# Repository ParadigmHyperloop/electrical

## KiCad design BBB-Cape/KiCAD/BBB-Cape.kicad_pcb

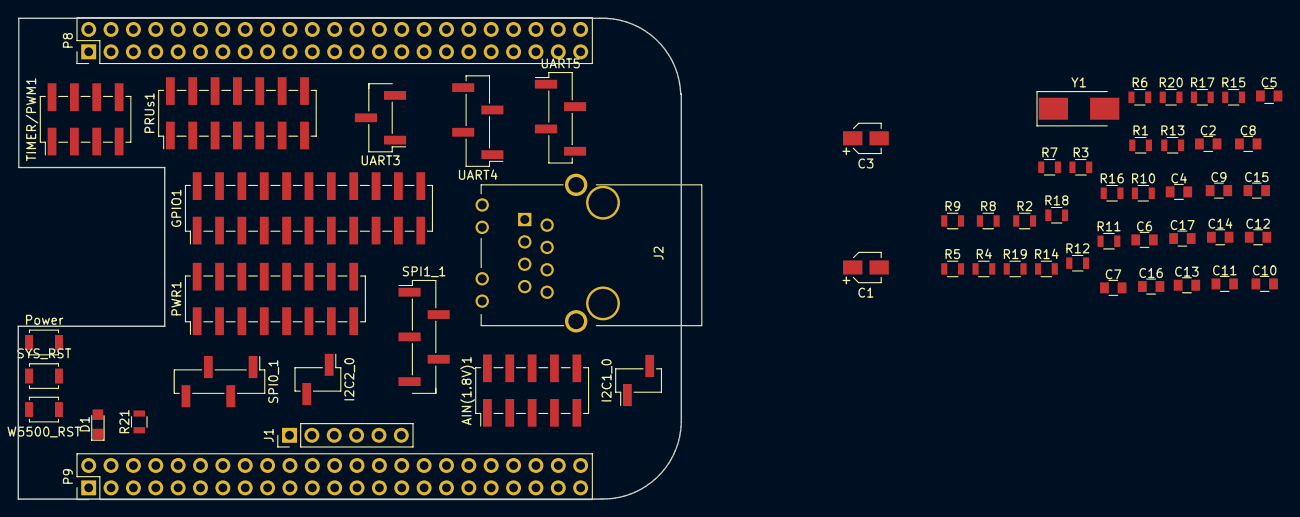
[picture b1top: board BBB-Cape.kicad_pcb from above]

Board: 2 copper layers, 75.3 x 54.6 mm, 60 parts (1 on the bottom side), 109 nets, no tracks yet.

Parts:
AIN(1.8V)1: Conn_02x05_Odd_Even; Pin_Header_Straight_2x05_Pitch2.54mm_SMD
C1, C3: 10uF; CP_Elec_3x5.3
C2, C4, C5, C6, C7, C8, C9: 0.1uF; C_0805
C10, C11: 6.8nF; C_0805
C12, C15: 10nF; C_0805
C13: 22nF; C_0805
C14: 4.7uF; C_0805
C16, C17: 18pF; C_0805
D1: LED; LED_0805
GPIO1: Conn_02x11_Odd_Even; Pin_Header_Straight_2x11_Pitch2.54mm_SMD
I2C1_0, I2C2_0: Conn_01x02; Pin_Header_Straight_1x02_Pitch2.54mm_SMD_Pin1Left
J1: 01x06_Stackable Header; Pin_Header_Straight_1x06_Pitch2.54mm
J2: RJ45-TRANSFO; RJ45_TRANSFO
P8, P9: 02x23_Stackable Header; Pin_Header_Straight_2x23_Pitch2.54mm
PRUs1: Conn_02x07_Odd_Even; Pin_Header_Straight_2x07_Pitch2.54mm_SMD
PWR1: Conn_02x08_Odd_Even; Pin_Header_Straight_2x08_Pitch2.54mm_SMD
R1, R2: 49.9; R_0805
R3: 10; R_0805
R4, R5, R21: 330; R_0805
R6, R7: 82; R_0805
R8: 12.4k; R_0805
R9, R10, R11, R12, R13, R14, R15, R16, R17, R18, R19: 10k; R_0805
R20: 10M; R_0805
SPI0_1: Conn_01x04; Pin_Header_Straight_1x04_Pitch2.54mm_SMD_Pin1Left
SPI1_1: Conn_01x05; Pin_Header_Straight_1x05_Pitch2.54mm_SMD_Pin1Left
SW1: W5500_RST; SW_SPST_B3U-1000P
SW2: SYS_RST; SW_SPST_B3U-1000P
SW3: Power; SW_SPST_B3U-1000P
TIMER/PWM1: Conn_02x04_Odd_Even; Pin_Header_Straight_2x04_Pitch2.54mm_SMD
U1: WIZnet W5500; LQFP-48_7x7mm_Pitch0.5mm
UART3: Conn_01x03; Pin_Header_Straight_1x03_Pitch2.54mm_SMD_Pin1Left
UART4, UART5: Conn_01x04; Pin_Header_Straight_1x04_Pitch2.54mm_SMD_Pin1Left
Y1: 25MHz; Crystal_SMD_0603-2pin_6.0x3.5mm_HandSoldering

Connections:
3V3D: C1.1, C2.1, R19.1, U1.28
ACT_LED: R4.1, U1.27
AIN0: AIN(1.8V)1.7, P9.39
AIN1: AIN(1.8V)1.6, P9.40
AIN2: AIN(1.8V)1.5, P9.37
AIN3: AIN(1.8V)1.4, P9.38
AIN4: AIN(1.8V)1.1, P9.33
AIN5: AIN(1.8V)1.2, P9.36
AIN6: AIN(1.8V)1.3, P9.35
DGND: C3.2, C4.2, C5.2, C6.2, C7.2, C8.2, C9.2, C12.2, C13.2, C14.2, C15.2, C16.2, C17.2, GPIO1.21, GPIO1.22, J1.1, P8.1, P8.2, P9.1, P9.2, P9.43, P9.44, P9.45, P9.46, PWR1.2, PWR1.4, PWR1.6, PWR1.8, PWR1.10, PWR1.12, PWR1.14, PWR1.16, R8.2, R9.1, R13.1, R14.1, R15.1, R16.1, R17.1, R21.2, SW1.2, SW2.2, SW3.2, U1.3, U1.9, U1.14, U1.16, U1.19, U1.29, U1.48
EHRPWM1A: P9.14, TIMER/PWM1.5
EHRPWM1B: P9.16, TIMER/PWM1.7
EHRPWM2A: P8.19, P8.45, TIMER/PWM1.6
EHRPWM2B: P8.13, P8.46, TIMER/PWM1.8
GNDA_ADC: AIN(1.8V)1.9, AIN(1.8V)1.10, P9.34
GPIO49: GPIO1.15, P9.23
GPIO_26: GPIO1.6, P8.14
GPIO_27: GPIO1.7, P8.17
GPIO_32: GPIO1.11, P8.25
GPIO_33: GPIO1.14, P8.24
GPIO_34: GPIO1.3, P8.5
GPIO_35: GPIO1.4, P8.6
GPIO_36: GPIO1.9, P8.23
GPIO_37: GPIO1.12, P8.22
GPIO_38: GPIO1.1, P8.3
GPIO_39: GPIO1.2, P8.4
GPIO_46: GPIO1.8, P8.16
GPIO_47: GPIO1.5, P8.15
GPIO_48: GPIO1.13, P9.15
GPIO_60: GPIO1.18, P9.12
GPIO_61: GPIO1.16, P8.26
GPIO_65: GPIO1.10, P8.18
GPIO_115: GPIO1.19, P9.27
GPIO_117: GPIO1.17, P9.25
I2C1_SCL/SPI0_CS0: P9.17, SPI0_1.4
I2C1_SCL/UART1_TXD: I2C1_0.1, P9.24
I2C1_SDA/SPI0_DI: P9.18, SPI0_1.2
I2C1_SDA/UART1_RXD: I2C1_0.2, P9.26
I2C2_SCL/SPI0_DO/UART2_TXD: I2C2_0.1, P9.21, SPI0_1.1
I2C2_SCL/SPI1_CS1/UART1_RTSn: P9.19, SPI1_1.5
I2C2_SDA/SPIO_SCLK/UART2_RXD: I2C2_0.2, P9.22, SPI0_1.3
LINK_LED: R5.1, U1.25
unnamed: C1.2, C2.2
unnamed: C10.1, J2.4
unnamed: C11.1, J2.6
unnamed: C12.1, J2.5, R6.2, R7.2
unnamed: C13.1, J2.2, R3.2
unnamed: C14.1, U1.20
unnamed: C15.1, U1.22
unnamed: C16.1, R20.1, U1.30, Y1.1
unnamed: C17.1, R20.2, U1.31, Y1.2
unnamed: D1.1, R21.1
unnamed: J2.GK, R4.2
unnamed: J2.YK, R5.2
unnamed: R8.1, U1.10
unnamed: R9.2, U1.23
unnamed: R10.2, U1.45
unnamed: R11.2, U1.44
unnamed: R12.2, U1.43
unnamed: R13.2, U1.42
unnamed: R14.2, U1.41
unnamed: R15.2, U1.40
unnamed: R16.2, U1.39
unnamed: R17.2, U1.38
PRU0_14OUT: P8.12, PRUs1.2
PRU0_15OUT: P8.11, PRUs1.1
PRU1_2: P8.43, PRUs1.13
PRU1_3: P8.44, PRUs1.14
PRU1_4: P8.41, PRUs1.11
PRU1_5: P8.42, PRUs1.12
PRU1_6: P8.39, PRUs1.9
PRU1_7: P8.40, PRUs1.10
PRU1_8: P8.27, PRUs1.5
PRU1_9: P8.29, PRUs1.7
PRU1_10: P8.28, PRUs1.6
PRU1_11: P8.30, PRUs1.8
PRU1_12: P8.21, PRUs1.3
PRU1_13: P8.20, PRUs1.4
PWR_BUT: P9.9, SW3.1
RX+: C10.2, R7.1, U1.6
RX-: C11.2, R6.1, U1.5
SPI1_CS0: P9.28, SPI1_1.4, U1.32
SPI1_CS1/UART3_TXD: P9.42, UART3.1
SPI1_D0: P9.29, SPI1_1.1
SPI1_DI: P9.30, SPI1_1.2, U1.34
SPI1_SCLK: P9.31, SPI1_1.3, U1.33
SYS_5V: P9.7, P9.8
SYS_RESETn: P9.10, SW2.1
TIMER4: P8.7, TIMER/PWM1.1
TIMER5: P8.9, TIMER/PWM1.3
TIMER6: P8.10, TIMER/PWM1.4
TIMER7: P8.8, TIMER/PWM1.2
TX+: J2.1, R1.2, U1.2
TX-: J2.3, R2.2, U1.1
UART3_CTSn: P8.36, UART3.3
UART3_RTSn: P8.34, UART3.2
UART4_CTSn: P8.35, UART4.4
UART4_RTSn: P8.33, UART4.3
UART4_RXD: P9.11, UART4.2
UART4_TXD: P9.13, UART4.1
UART5_CTSn+: P8.31, UART5.4
UART5_RTSn: P8.32, UART5.3
UART5_RXD+: P8.38, UART5.2
UART5_TXD+: P8.37, UART5.1
VDD_3V3: C3.1, C4.1, C5.1, C6.1, C7.1, C8.1, C9.1, D1.2, J2.GA, J2.YA, P9.3, P9.4, PWR1.9, PWR1.11, PWR1.13, PWR1.15, R1.1, R2.1, R3.1, R10.1, R11.1, R12.1, R18.1, U1.4, U1.8, U1.11, U1.15, U1.17, U1.21
VDD_5V: GPIO1.20, P9.5, P9.6, PWR1.1, PWR1.3, PWR1.5, PWR1.7
VDD_ADC: AIN(1.8V)1.8, P9.32
W5500_INT: P9.41, R19.2, U1.36
W5500_RST: R18.2, SW1.1, U1.37

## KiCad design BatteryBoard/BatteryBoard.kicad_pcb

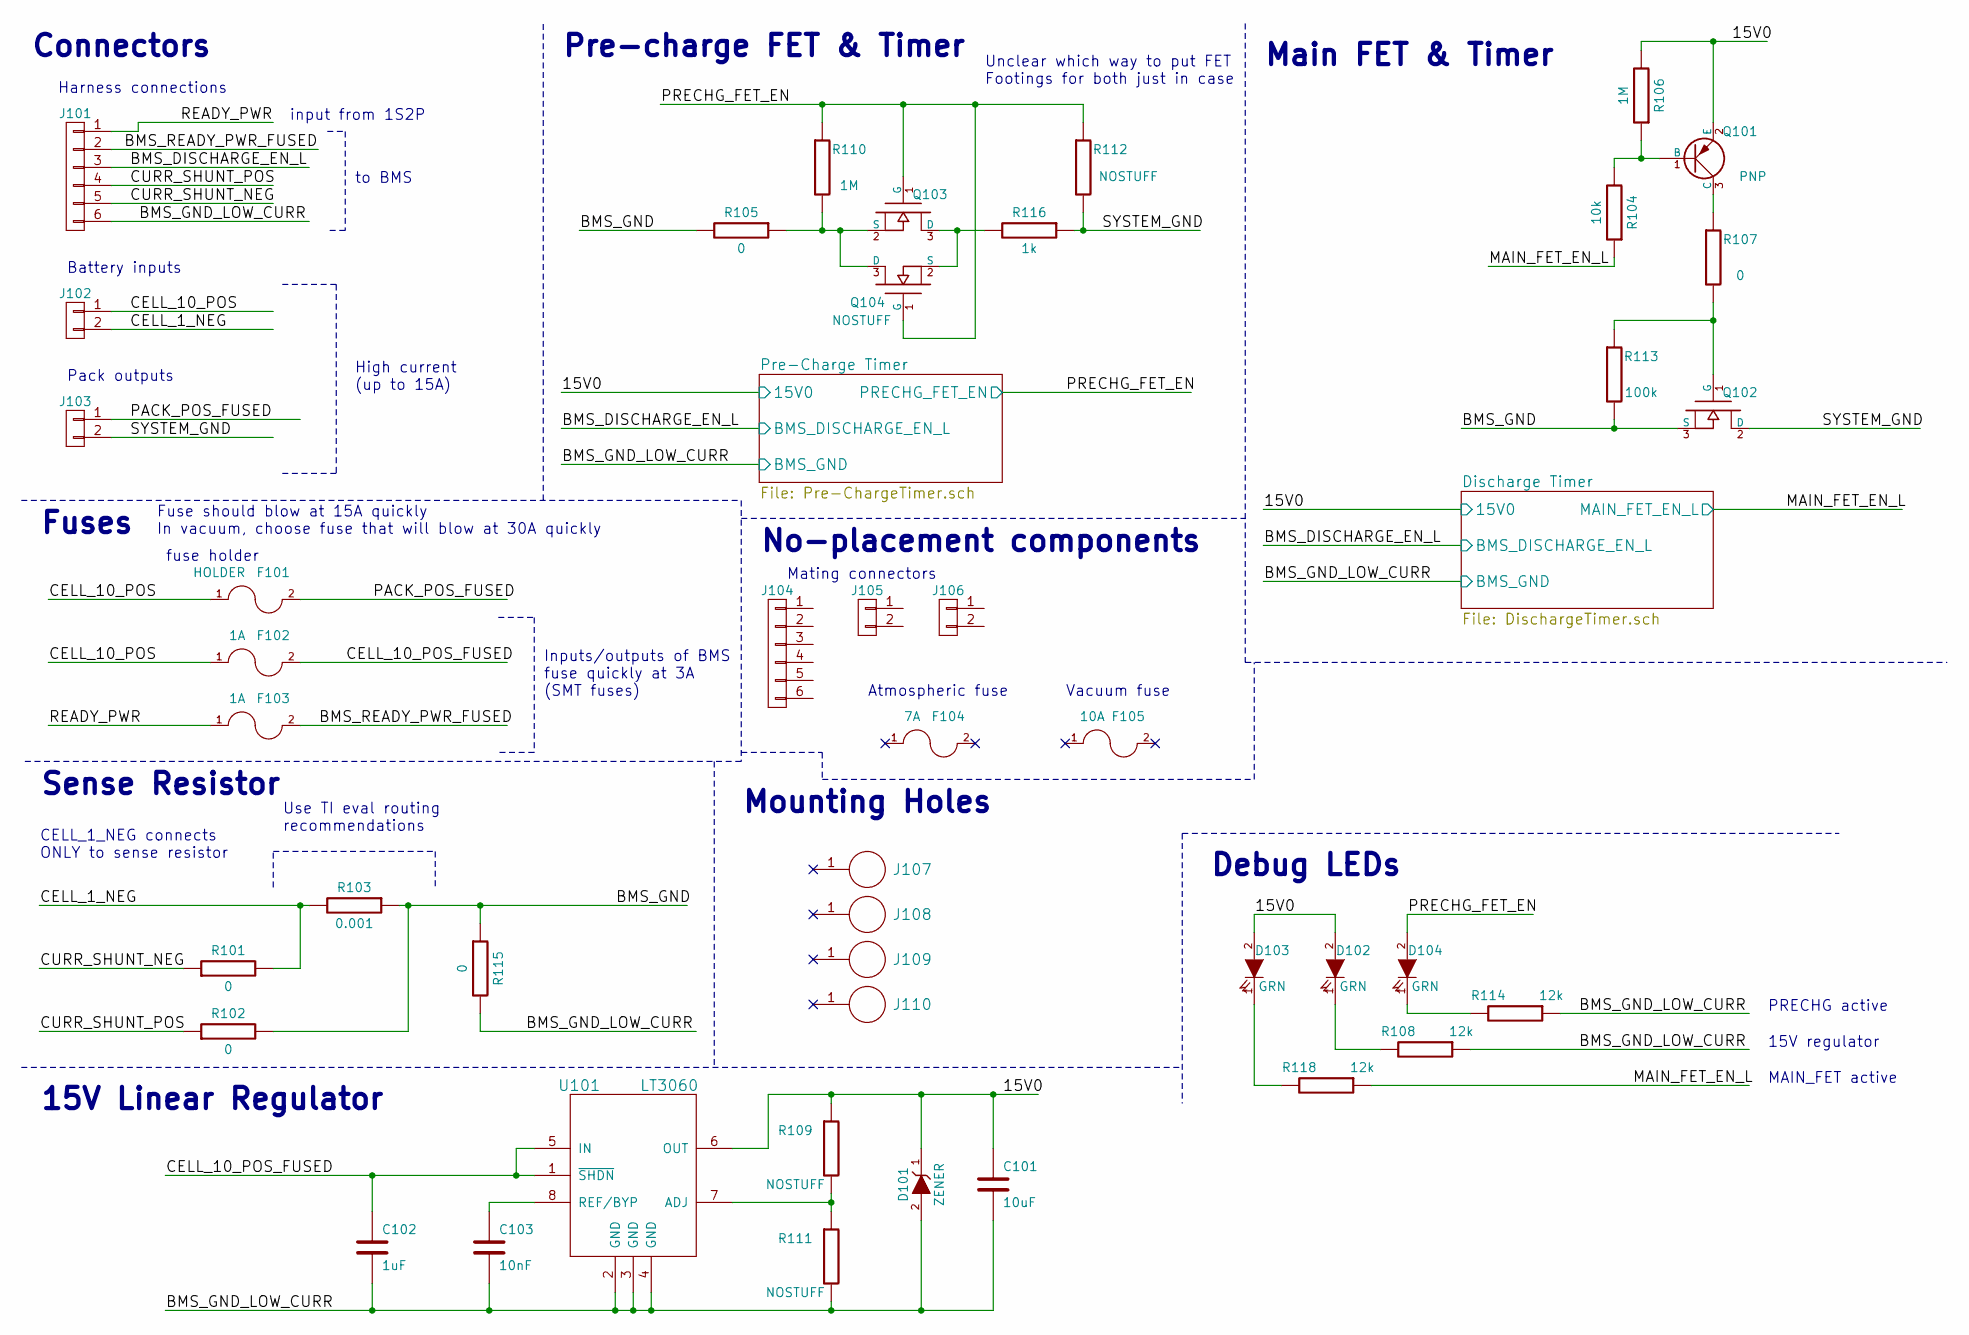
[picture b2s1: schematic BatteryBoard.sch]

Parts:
C101: 10uF; C_1206_HandSoldering; Mfg. PN CL31B106KAHNNNE; Digi-Key PN 1276-1804-1-ND
C102: 1uF; C_1206_HandSoldering; Mfg. PN CL31B105KCHNNNE; Digi-Key PN 1276-1838-1-ND
C103: 10nF; C_0805_HandSoldering
D101: ZENER; D_SOD-523; Mfg. PN BZT585B18T-7; Digi-Key PN BZT585B18T-7DICT-ND
D102, D103, D104: GRN; LED_1206_HandSoldering
F101: HOLDER; Fuseholder_5x20mm_Wurth; Mfg. PN 696103201002; Digi-Key PN 732-11372-ND
F102, F103: 1A; Fuse_SMD_2410; Mfg. PN 0679H1000-05; Digi-Key PN 507-2046-2-ND
F104: 7A; Mfg. PN 5TT 7-R; Digi-Key PN 507-1301-ND
F105: 10A; Mfg. PN 0034.0911; Digi-Key PN 486-2503-ND
J101: CONN_01X06; CONN_PHOENIX_1844252_6PIN; Mfg. PN 1844252; Digi-Key PN 277-2427-ND
J102, J103: CONN_01X02; CONN_PHOENIX_1923869_2PIN; Mfg. PN 1923869; Digi-Key PN 277-6570-ND
J104: CONN_01X06; Mfg. PN 1862894; Digi-Key PN 277-6439-ND
J105, J106: CONN_01X02; Mfg. PN 1912401; Digi-Key PN 277-14370-ND
J107, J108, J109, J110: MOUNTING_HOLE; MountingHole_5.5mm_Pad_Via
Q101: PNP; SOT-23_Handsoldering; Mfg. PN MMBTA92; Digi-Key PN MMBTA92FSCT-ND
Q102: AOB290L; DD-PAK_TO263_AOB290L; Mfg. PN AOB290L; Digi-Key PN 785-1329-1-ND
Q103: MOS_N; SOT-23_Handsoldering; Mfg. PN BSS123; Digi-Key PN BSS123NCT-ND
Q104: NOSTUFF; SOT-23_Handsoldering
R101, R102, R107: 0; R_0805_HandSoldering
R103: 0.001; RSNS_VISHAY_WSR21L000FEA; Mfg. PN WSR21L000FEA; Digi-Key PN WSRA-.001CT-ND
R104: 10k; R_0805_HandSoldering
R105: 0; R_2512_HandSoldering
R106: 1M; R_0805_HandSoldering
R108, R114, R118: 12k; R_0805_HandSoldering
R109, R111, R112: NOSTUFF; R_0805_HandSoldering
R110: 1M; R_0805_HandSoldering; Mfg. PN CRCW08051M00FKEA; Digi-Key PN 541-1.00MCCT-ND
R113: 100k; R_0805_HandSoldering; Mfg. PN CRCW08051M00FKEA; Digi-Key PN 541-1.00MCCT-ND
R115: 0; R_1206_HandSoldering
R116: 1k; R_2512_HandSoldering; Mfg. PN CRM2512-JW-102ELF; Digi-Key PN CRM2512-JW-102ELFCT-ND
U101: LT3060; Mfg. PN LT3060ETS8-15#TRMPBF; Digi-Key PN LT3060ETS8-15#TRMPBFCT-ND

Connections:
/15V0: C101.1, D101.1 (A), D102.2 (K), D103.2 (K), Q101.2 (E), R106.2, R109.1, U101.6 (OUT); also elsewhere on the board
/BMS_DISCHARGE_EN_L: J101.3; also elsewhere on the board
/BMS_GND: Q102.3 (S), R102.2, R103.1, R105.2, R113.2, R115.1
/BMS_GND_LOW_CURR: C101.2, C102.2, C103.2, D101.2 (K), J101.6, R108.1, R111.2, R114.1, R115.2, U101.2 (GND), U101.3 (GND), U101.4 (GND); also elsewhere on the board
/BMS_READY_PWR_FUSED: F103.2, J101.2
/CELL_1_NEG: J102.2, R101.2, R103.2
/CELL_10_POS: F101.1, F102.1, J102.1
/CELL_10_POS_FUSED: C102.1, F102.2, U101.1 (~SHDN), U101.5 (IN)
/CURR_SHUNT_NEG: J101.5, R101.1
/CURR_SHUNT_POS: J101.4, R102.1
/MAIN_FET_EN_L: R104.1, R118.1; also elsewhere on the board
/PACK_POS_FUSED: F101.2, J103.1
/PRECHG_FET_EN: D104.2 (K), Q103.1 (G), Q104.1 (G), R110.1, R112.1; also elsewhere on the board
/READY_PWR: F103.1, J101.1
/SYSTEM_GND: J103.2, Q102.2 (D), R112.2, R116.1
unnamed: C103.1, U101.8 (REF/BYP)
unnamed: D102.1 (A), R108.2
unnamed: D103.1 (A), R118.2
unnamed: D104.1 (A), R114.2
unnamed: Q101.1 (B), R104.2, R106.1
unnamed: Q101.3 (C), R107.1
unnamed: Q102.1 (G), R107.2, R113.1
unnamed: Q103.2 (S), Q104.3 (D), R105.1, R110.2
unnamed: Q103.3 (D), Q104.2 (S), R116.2
unnamed: R109.2, R111.1, U101.7 (ADJ)

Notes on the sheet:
Battery inputs
Harness connections
Pack outputs
Connectors
High current (up to 15A)
Sense Resistor
Use TI eval routing recommendations
15V Linear Regulator
Main FET & Timer
Pre-charge FET & Timer
Debug LEDs
Fuses
input from 1S2P
to BMS
Fuse should blow at 15A quickly In vacuum, choose fuse that will blow at 30A quickly
Inputs/outputs of BMS fuse quickly at 3A (SMT fuses)
CELL_1_NEG connects ONLY to sense resistor
PRECHG active
15V regulator
MAIN_FET active
No-placement components
fuse holder
Atmospheric fuse
Vacuum fuse
Unclear which way to put FET Footings for both just in case
Mating connectors
Mounting Holes

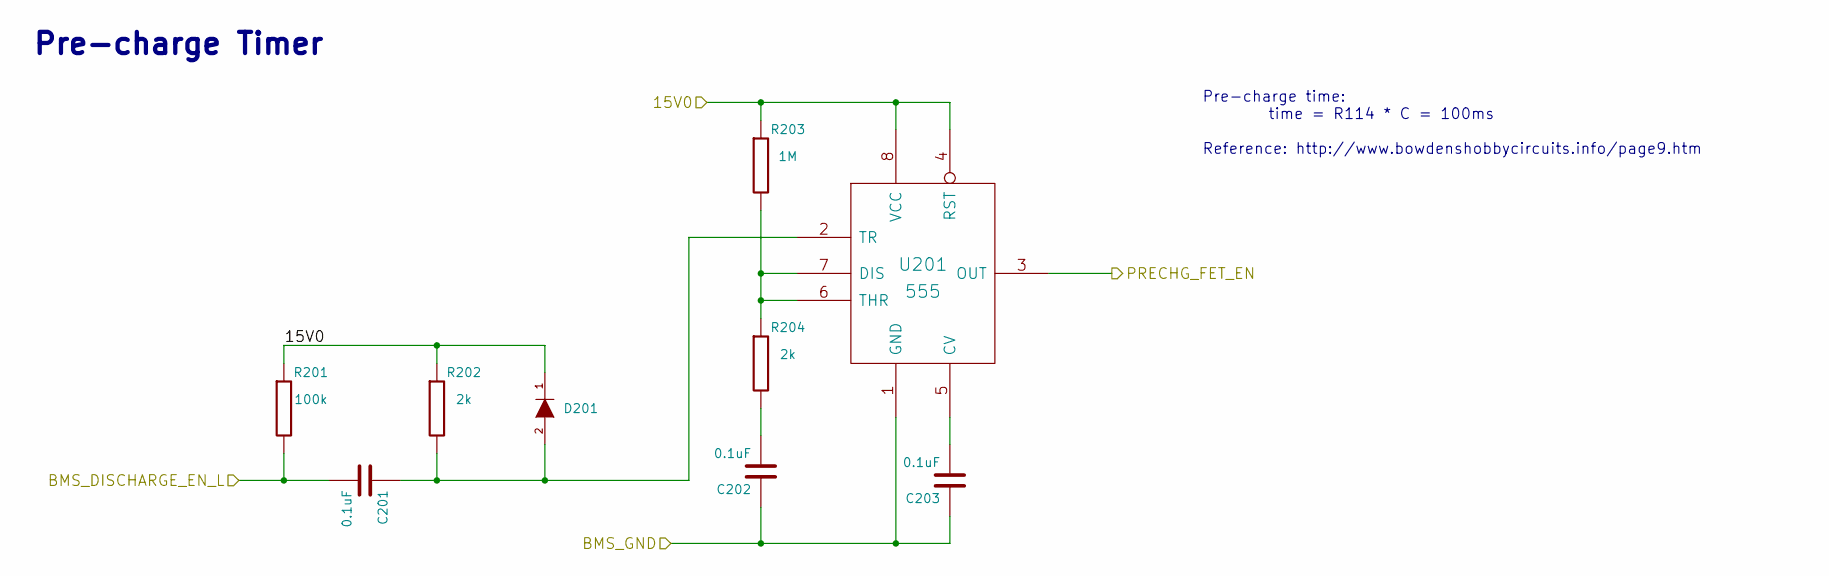
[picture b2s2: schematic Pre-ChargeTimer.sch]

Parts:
C201, C202, C203: 0.1uF; C_0805_HandSoldering
D201: DIODE; D_SOD-523; Mfg. PN 1N4148X-TP; Digi-Key PN 1N4148XTPMSCT-ND
R201: 100k; R_0805_HandSoldering
R202, R204: 2k; R_0805_HandSoldering
R203: 1M; R_0805_HandSoldering
U201: 555; SOIC-8_3.9x4.9mm_Pitch1.27mm; Mfg. PN LMC555CMX/NOPB; Digi-Key PN LMC555CMX/NOPBCT-ND

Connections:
/15V0: D201.1 (K), R201.1, R202.1, R203.1, U201.4 (RST), U201.8 (VCC); also elsewhere on the board
/BMS_DISCHARGE_EN_L: C201.2, R201.2; also elsewhere on the board
/BMS_GND_LOW_CURR: C202.1, C203.1, U201.1 (GND); also elsewhere on the board
/PRECHG_FET_EN: U201.3 (OUT); also elsewhere on the board
unnamed: C201.1, D201.2 (A), R202.2, U201.2 (TR)
unnamed: C202.2, R204.2
unnamed: C203.2, U201.5 (CV)
unnamed: R203.2, R204.1, U201.6 (THR), U201.7 (DIS)

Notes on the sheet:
Pre-charge Timer
Pre-charge time: time = R114 * C = 100ms Reference: http://www.bowdenshobbycircuits.info/page9.htm

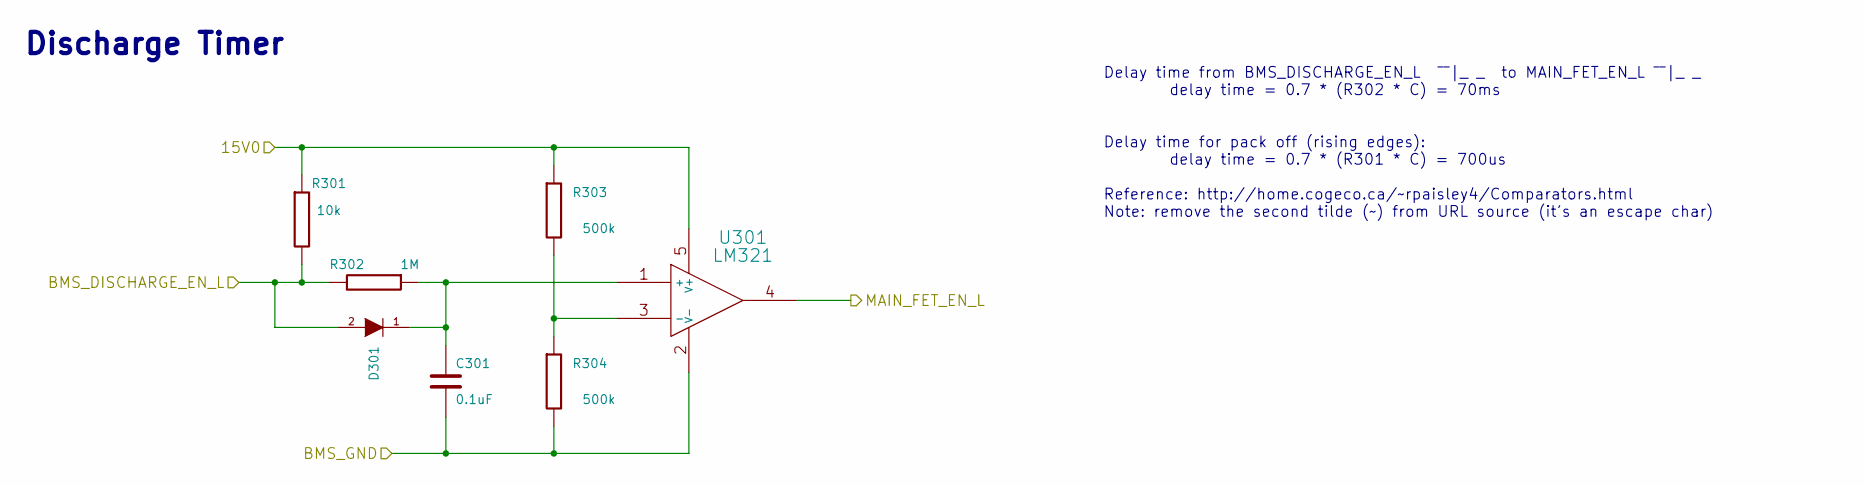
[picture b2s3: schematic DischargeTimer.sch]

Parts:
C301: 0.1uF; C_0805_HandSoldering
D301: DIODE; D_SOD-523; Mfg. PN 1N4148X-TP; Digi-Key PN 1N4148XTPMSCT-ND
R301: 10k; R_0805_HandSoldering
R302: 1M; R_0805_HandSoldering
R303, R304: 500k; R_0805_HandSoldering
U301: LM321; SOT-23-5_HandSoldering; Mfg. PN LM321MFX/NOPB; Digi-Key PN LM321MFX/NOPBCT-ND

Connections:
/15V0: R301.1, R303.1, U301.5 (V+); also elsewhere on the board
/BMS_DISCHARGE_EN_L: D301.2 (A), R301.2, R302.2; also elsewhere on the board
/BMS_GND_LOW_CURR: C301.2, R304.2, U301.2 (V-); also elsewhere on the board
/MAIN_FET_EN_L: U301.4; also elsewhere on the board
unnamed: C301.1, D301.1 (K), R302.1, U301.1 (+)
unnamed: R303.2, R304.1, U301.3 (-)

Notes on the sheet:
Discharge Timer
Delay time from BMS_DISCHARGE_EN_L ¯¯|_ _ to MAIN_FET_EN_L ¯¯|_ _ delay time = 0.7 * (R302 * C) = 70ms Delay time for pack off (rising edges): delay time = 0.7 * (R301 * C) = 700us Reference: http://home.cogeco.ca/~~rpaisley4/Comparators.html Note: remove the second tilde (~~) from URL source (it's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

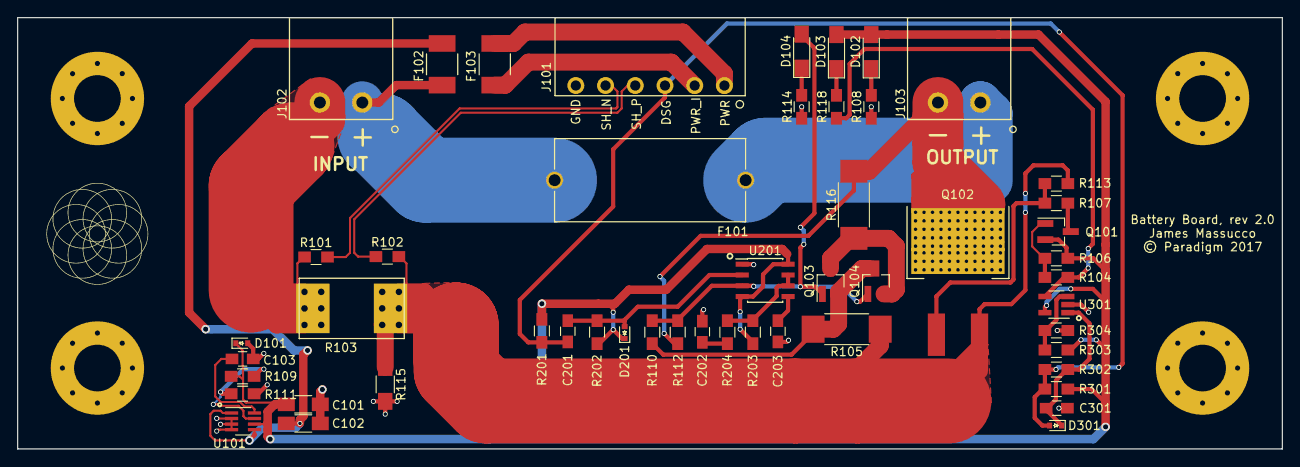
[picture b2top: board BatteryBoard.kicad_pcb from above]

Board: 2 copper layers, 149.0 x 50.8 mm, 55 parts (0 on the bottom side), 31 nets.

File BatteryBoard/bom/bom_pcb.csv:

Item,Reference(s),Value,Quantity,Digi-Key PN,Mfg.,Mfg. PN
1,C101,10uF,1,1276-1804-1-ND,Samsung,CL31B106KAHNNNE
2,C102,1uF,1,1276-1838-1-ND,Samsung,CL31B105KCHNNNE
3,C103,10nF,1,,,
4,C201 C202 C203,0.1uF,3,,,
5,C301,68nF,1,,,
6,D101,ZENER,1,,,
7,D102 D103,GRN,2,,,
8,D104,RED,1,,,
9,D201 D301,DIODE,2,1N4148XTPMSCT-ND,Micro,1N4148X-TP
10,F101 F104,7A,2,732-11372-ND,Wurth Electronics,696103201002
11,F102 F103,1A,2,507-2046-2-ND,Bel Fuse,0679H1000-05
12,F105,10A,1,486-2503-ND,Schurter,0034.0911
13,J101 J104,CONN_01X06,2,277-2427-ND,Phoenix,1844252
14,J102 J103 J105 J106,CONN_01X02,4,277-6570-ND,Phoenix,1923869
15,J107 J108 J109 J110,MOUNTING_HOLE,4,,,
16,Q101,PNP,1,MMBTA92FSCT-ND,Fairchild,MMBTA92
17,Q102,AOB290L,1,785-1329-1-ND,Alpha & Omega,AOB290L
18,Q103,MOS_N,1,BSS123NCT-ND,Fairchild,BSS123
19,Q104,NOSTUFF,1,,,
20,R101 R102 R105 R107 R115,0,5,,,
21,R103,0.001,1,WSRA-.001CT-ND,Vishay Dale,WSR21L000FEA
22,R104 R301,10k,2,,,
23,R106 R110 R203 R302,1M,4,541-1.00MCCT-ND,Vishay Dale,CRCW08051M00FKEA
24,R108 R114 R118,R,3,,,
25,R109 R111 R112,NOSTUFF,3,,,
26,R113 R201,100k,2,541-1.00MCCT-ND,Vishay Dale,CRCW08051M00FKEA
27,R116,1k,1,,,
28,R202,2k,1,,,
29,R204,2.2k,1,,,
30,R303 R304,500k,2,,,
31,U101,LT3060,1,,,
32,U201,555,1,LMC555CMX/NOPBCT-ND,Texas Instruments,LMC555CMX/NOPB
33,U301,LM321,1,LM321MFX/NOPBCT-ND,Texas Instruments,LM321MFX/NOPB

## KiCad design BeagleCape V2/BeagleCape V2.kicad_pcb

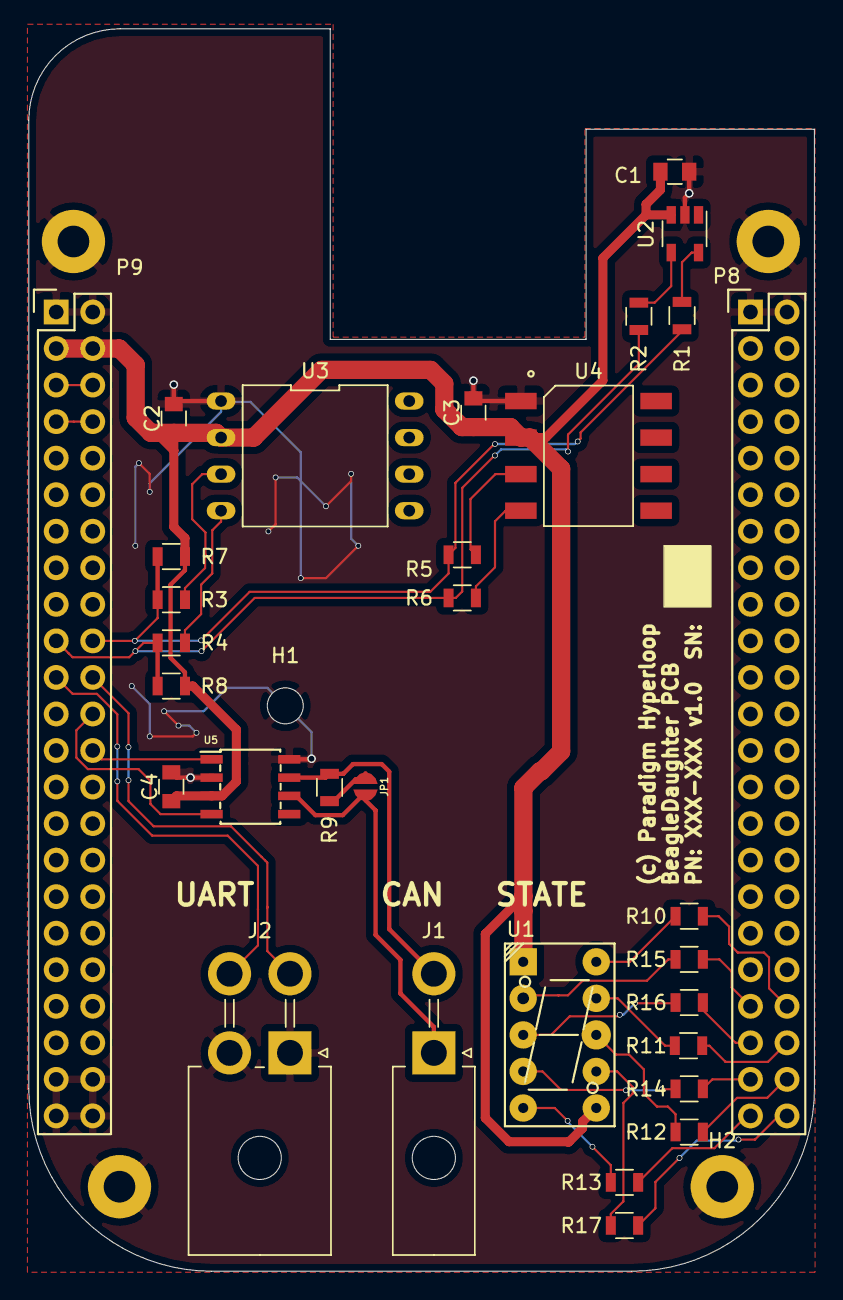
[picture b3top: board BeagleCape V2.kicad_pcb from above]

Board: 2 copper layers, 54.6 x 86.4 mm, 36 parts (0 on the bottom side), 35 nets.

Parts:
C1, C2, C3, C4: 0.1u; C_0805
H1: M3; MountingHole_2.5mm
H2, H3, H4, H5: M2; MountingHole_2.2mm_M2_Pad
J1: CAN; Molex_MiniFit-JR-5569-02A2_2x01x4.20mm_Angled
J2: Conn_01x04; Molex_MiniFit-JR-5569-04A2_2x02x4.20mm_Angled
JP1: Open; JUMPER_EGG
P8, P9: BeagleBone_Black_Header; Socket_BeagleBone_Black
R1, R2, R3, R4, R5, R6: 0; R_0805
R7, R8: 4k7; R_0805
R9: 120; R_0805
R10, R11, R12, R13, R14, R15, R16, R17: 300; R_0805
U1: HDSP-A151; HDSP-78xx
U2: TC74A0-3.3VCTTR; TSOT-23-5
U3: HSCDANN030PA2A3; DIP8_2.54_W13.8
U4: HSCMAND060PA3A3; SOIC-8-2.54-W9.4
U5: SN65HVD230; SOIC-8_N

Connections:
+3V3: C1.1, C2.1, C3.1, C4.1, P9.3, P9.4, R7.1, R8.1, U1.1, U1.6, U2.3, U3.2, U4.2, U5.3
+5V: P9.5, P9.6
/CAN_H: J1.2, R9.2, U5.7
/CAN_L: J1.1, JP1.2, U5.6
/CAN_RD: P9.24, U5.4
/CAN_TD: P9.26, U5.1
/I2C2_SCL: P9.19, R2.1, R4.1, R6.1, R8.2
/I2C2_SDA: P9.20, R1.1, R3.1, R5.1, R7.2
/UART2_RXD: J2.3, P9.22
/UART2_TXD: J2.4, P9.21
/sevseg_A: P8.40, R10.2
/sevseg_B: P8.42, R11.2
/sevseg_C: P8.44, R12.2
/sevseg_D: P8.45, R13.2
/sevseg_DP: P8.46, R17.2
/sevseg_E: P8.43, R14.2
/sevseg_F: P8.39, R15.2
/sevseg_G: P8.41, R16.2
GNDD: C1.2, C2.2, C3.2, C4.2, H1.1, H2.1, H3.1, H4.1, H5.1, J2.1, J2.2, P8.1, P8.2, P9.1, P9.2, P9.43, P9.44, P9.45, P9.46, U2.2, U3.1, U4.1, U5.2, U5.8
unnamed: JP1.1, R9.1
unnamed: R1.2, U2.5
unnamed: R2.2, U2.4
unnamed: R3.2, U3.3
unnamed: R4.2, U3.4
unnamed: R5.2, U4.3
unnamed: R6.2, U4.4
unnamed: R10.1, U1.10
unnamed: R11.1, U1.9
unnamed: R12.1, U1.8
unnamed: R13.1, U1.5
unnamed: R14.1, U1.4
unnamed: R15.1, U1.2
unnamed: R16.1, U1.3
unnamed: R17.1, U1.7
SYS_5V: P9.7, P9.8

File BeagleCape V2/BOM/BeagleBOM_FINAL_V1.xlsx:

BOM
Item # | Quantitiy | Value | References | Package | Description | Manufacturer | Manufacturer PN | Supplier | Supplier PN | Unit Cost [$CAD] | Extended [$CAD] | Notes: | Alternates
1.0 | 1.0 | BeagleBone_Black_Header | P8 P9 | Socket_BeagleBone_Black:Socket_BeagleBone_Black | . |  |  | Digi-Key | 1528-1365-ND
4.0 | 10.0 | 0.0 | R3 R4 R5 R6 R1 R2 | Resistors_SMD:R_0805 | . |  |  |  | 311-0.0ARCT-ND
5.0 | 2.0 | 4k7 | R7 R8 | Resistors_SMD:R_0805 | . |  |  |  | 311-4.7KARCT-ND
6.0 | 10.0 | 0.1u | C1 C2 C3 C4 | Capacitors_SMD:C_0805 | . |  |  |  | 732-8045-1-ND
9.0 | 1.0 | TC74A0-3.3VCTTR | U2 | TO_SOT_Packages_SMD:TSOT-23-5 | . |  |  |  | TC74A0-3.3VCTCT-ND
10.0 | 1.0 | HDSP-A151 | U1 | Displays_7-Segment:HDSP-78xx | . |  |  |  | 516-3243-ND
11.0 | 1.0 | SN65HVD230 | U5 | µ104KiCAD_IC:SOIC-8_N | . |  |  |  | 296-11654-1-ND
12.0 | 1.0 | 120.0 | R9 | Resistors_SMD:R_0805 | . |  |  |  | 311-120ARCT-ND
11.0 | 2.0 | CAN | J1 |  | CONN RECEPT 2POS DUAL |  |  | Digi-Key | WM3700-ND |  |  | Mini Fit Jr. 2 Pos Housing
12.0 | 2.0 | UART | J2 |  | CONN RECEPT 4POS DUAL |  |  | Digi-Key | WM3701-ND |  |  | Mini Fit Jr. 4 Pos Housing
15.0 | 10.0 | 300.0 | R10 - R17 | Resistors_SMD:R_0805 | . |  |  |  | 311-300ARCT-ND
10.0 | 25.0 |  |  |  | CONN SOCKET 18-24AWG CRIMP TIN |  |  | Digi-Key | WM2501CT-ND |  |  | Mini Fit Jr. Crimp
11.0 | 1.0 | CAN | J1 |  | CONN RECEPT 2POS DUAL |  |  | Digi-Key | WM1351-ND |  |  | Mini Fit Jr. 2 Pos Housing
12.0 | 1.0 | UART | J2 |  | CONN RECEPT 4POS DUAL |  |  | Digi-Key | WM1352-ND |  |  | Mini Fit Jr. 4 Pos Housing
3.0 | 1.0 | HSCDANN030PA2A3 | U3 | BeagleCape V2-STRIDE:DIP8_2.54_W13.8 | . |  | HSCDANN030PA2A3 |  | HSCDANN030PA2A3-ND |  |  |  | 785-HSCDANN030PA2A3 | Mouser
7.0 | 1.0 | HSCMAND060PA3A3 | U4 | BeagleCape V2-STRIDE:SOIC-8-2.54-W9.4 | . |  | HSCMAND060PA3A3 |  | 480-5519-ND |  |  |  | 785-HSCMAND060PA3A3 | Mouser

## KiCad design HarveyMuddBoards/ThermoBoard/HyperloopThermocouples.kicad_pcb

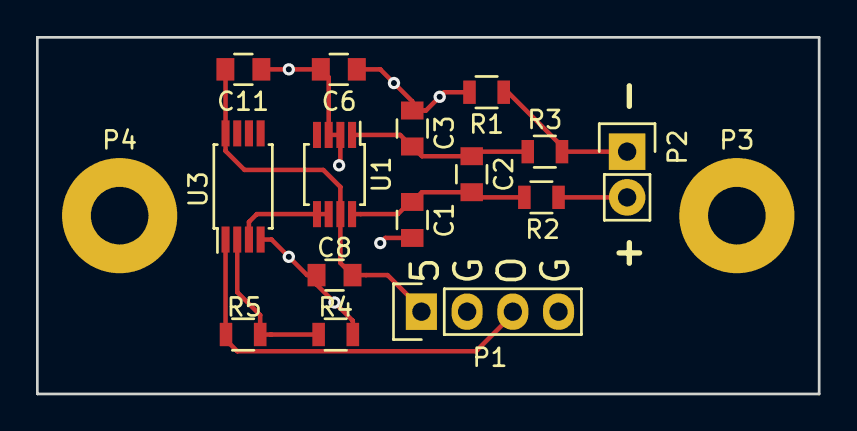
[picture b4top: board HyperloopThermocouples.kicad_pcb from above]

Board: 2 copper layers, 43.4 x 19.8 mm, 17 parts (0 on the bottom side), 9 nets.

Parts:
C1, C3: 0.5u; C_0805
C2, C6: 1u; C_0805
C8, C11: 0.1u; C_0805
P1: CONN_01X04; Pin_Header_Straight_1x04
P2: CONN_01X02; Pin_Header_Straight_1x02
P3, P4: CONN_01X01; MountingHole_3.2mm_M3_Pad
R1: 1meg; R_0805
R2, R3: 750; R_0805
R4: 10k; R_0805
R5: 4.5M; R_0805
U1: AD8495; MSOP-8_3x3mm_Pitch0.65mm
U3: TIRC4558IPWR; TSSOP-8_4.4x3mm_Pitch0.65mm

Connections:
/+5V: C8.1, C11.1, P1.1, U1.7, U3.8
/Out: P1.3, R5.2, U3.1
GND: C1.1, C3.2, C6.1, C6.2, C8.2, C11.2, P1.2, P1.4, P3.1, P4.1, R1.2, R4.1, U1.2, U1.3, U3.4
unnamed: C1.2, C2.1, R2.2, U1.8
unnamed: C2.2, C3.1, R3.2, U1.1
unnamed: P2.1, R1.1, R3.1
unnamed: P2.2, R2.1
unnamed: R4.2, R5.1, U3.2
unnamed: U1.5, U1.6, U3.3

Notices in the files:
BatteryBoard/BatteryBoard.kicad_pcb:
© Paradigm 2017
parts and their libraries:
Copyright 2016 Accelerated Designs. All rights reserved.
